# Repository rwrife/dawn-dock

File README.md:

A USB-powered ESP32-S3 bedside clock that keeps time and alarms offline, syncs user-approved schedules from a phone or PC, dims for sleep, and remains useful without internet.

## Overview

Dawn Dock sits between a basic alarm clock and a cloud-dependent smart display. Its core clock, alarm, snooze, brightness, and local setup functions work without an account or network. A companion app can transfer alarm schedules and calendar snapshots over the local network or BLE; optional weather and calendar refreshes are additive, never prerequisites for waking.

## Motivation

Traditional alarm clocks are dependable but tedious to configure. Smart displays are convenient but can depend on vendor accounts, internet services, microphones, and opaque data handling. Dawn Dock aims for a repairable middle path: physical controls, a calm night display, RTC-backed timekeeping, explicit sync, and documented offline behavior.

## Target users

- People who want a bedside clock without a cloud account or always-listening microphone.
- Shift workers, students, caregivers, and households with changing but non-critical routines.
- Makers who want an approachable ESP32-S3 and KiCad project with modular bring-up.
- Privacy-conscious users who want to own, inspect, back up, and export alarm data.

Dawn Dock is a convenience appliance, not a life-safety or medical device. Users must not rely on it for medication, emergency response, transportation safety, or any situation where a missed alarm could cause serious harm.

## Concrete use cases

1. Set recurring weekday alarms on the device with a rotary control and dedicated buttons.
2. Prepare a week of alarms on a phone or computer, review a diff, and explicitly sync it to the clock.
3. Import selected events from an `.ics` file and turn them into alarm suggestions that require confirmation.
4. Dim the screen manually or with an ambient-light rule while retaining a one-press brightness override.
5. Lose Wi-Fi overnight and still get the stored alarm from RTC-backed local state.
6. Export alarms, settings, and a redacted event snapshot as portable JSON.

## Intended workflow

1. Assemble the ESP32-S3 display module, low-voltage carrier board, controls, sensor, and enclosure.
2. Flash firmware over USB and complete first-run setup locally.
3. Set time from the companion app, USB serial, or network time; the RTC maintains time across normal power interruptions.
4. Create alarms on-device or in the companion app. Calendar-derived alarms are previews until accepted.
5. Review the device/app sync summary, transfer the schedule, and verify the next alarm on the clock face.
6. Use physical snooze, alarm-dismiss, brightness, and menu controls without opening the app.
7. Export or restore user-owned configuration when moving devices.

## MVP features

- RTC-backed local time, timezone, DST rules, and deterministic recurring alarms.
- 3.5-inch readable clock face with manual and ambient-light-aware dimming.
- Dedicated snooze and brightness controls plus a rotary menu control.
- Locally stored alarms with clear next-alarm and sync-state indicators.
- Local-only companion setup/sync, schedule preview, JSON backup, and `.ics` import.
- Versioned, authenticated local protocol with no required cloud account.
- Repeatable firmware/app builds and hardware-in-the-loop test points as the project matures.

## Non-goals

- No voice assistant, microphone monitoring, advertising, or remote cloud dashboard.
- No automatic alarm creation from calendar events without user confirmation.
- No news feed in the MVP; weather is optional and must fail quietly when offline.
- No battery operation beyond RTC backup in the first revision.
- No mains circuitry, custom AC adapter, medical claims, emergency alerts, or guaranteed wake-up claim.
- No attempt to compete with tablets or general-purpose smart displays.

## Hardware direction

The Rev A component gate selected an Espressif `ESP32-S3-DEVKITC-1-N8R8` controller, a separate Waveshare `29318` 3.5-inch capacitive-touch display, an Analog Devices `DS3231MZ+` RTC with a non-rechargeable CR2032, and a microphone-free MAX98357A audio path. The editable KiCad carrier schematic now provides controls, sensing, protected USB-C input, test access, and mounting intent. The integrated Waveshare `ESP32-S3-Touch-LCD-3.5` candidate was rejected because it includes a fitted microphone and does not expose all required internal test nodes.

The source-backed decision, dated price/availability snapshot, unresolved physical gates, and proposed GPIO map are in [component validation](docs/component-validation.md), [the preliminary BOM](bom/preliminary-bom.csv), and [the pin allocation](hardware/pin-allocation.csv).

The editable design tree is:

```text
hardware/kicad/dawn-dock.kicad_pro
hardware/kicad/dawn-dock.kicad_sch
hardware/kicad/dawn-dock.kicad_pcb  # routed Rev A0 review source
```

The project, schematic, and routed two-layer PCB exist and remain the design source of truth. Native ERC and DRC are clean and the review-only Gerber bundle is complete/aligned, but issue #4 remains on fabrication hold for received-unit geometry/orientation confirmation and unresolved EMC return-path/plane-coverage findings. PDF, render, and Gerber exports supplement but never replace editable sources.

Final electrical BOM data lives in KiCad schematic symbol properties (`Manufacturer`, `MPN`, supplier fields, notes) and is exported to `bom/bom.csv`. `bom/preliminary-bom.csv` is planning input/history, not the final electrical BOM.

## Privacy, permissions, and storage

- Device schedules and settings remain in local flash; the companion stores its local copy on the user's device.
- No account or telemetry is required. Network discovery and calendar/file access are requested only when the user invokes those workflows.
- Calendar import is file-based or user-selected; the MVP does not request broad calendar access by default.
- Sync is limited to the local network or BLE, uses an explicit pairing step, and presents changes before applying them.
- Backup/export uses documented JSON; calendar import uses `.ics`. Users can delete device/app state.
- Optional external data such as weather must be opt-in, disclose the contacted endpoint, and never affect alarm execution.

## Safety limits

- USB 5 V SELV power only; no mains wiring or charger design.
- Use a certified, enclosed USB power supply. Do not operate damaged cables or exposed assemblies unattended.
- RTC coin-cell support, if used, must follow the holder and cell manufacturer's polarity, chemistry, and charging restrictions.
- Audio output must be volume-limited and verified; the prototype is not a hearing or emergency alert device.
- Bench, simulation, and static-analysis results must be labeled separately. An unbuilt prototype is never described as physically tested.

## Architecture and verification baseline

The v0.1 documentation baseline freezes downstream design constraints while keeping unverified performance explicit:

- [System architecture and power allocation](docs/system-architecture.md)
- [Deterministic alarm semantics](docs/alarm-semantics.md)
- [MVP threat model](docs/threat-model.md)
- [Risk register](docs/risk-register.md)
- [Requirements verification matrix](docs/verification-matrix.md)
- [Hardware and product requirements](hardware/requirements.md)
- [Rev A component validation](docs/component-validation.md)
- [Manufacturer/source manifest](docs/source-manifest.csv)
- [Editable KiCad schematic, build, and verification](hardware/kicad/README.md)
- [Rev A schematic static review](docs/schematic-review.md)
- [Rev A0 PCB static layout review and fabrication hold](docs/pcb-layout-review.md)

The diagrams are editable Mermaid source. Results must be labeled as static analysis, simulation, software test, bench test, or field test; an absent physical test remains an open evidence gap.

## Current status and milestones

**Status: requirements, Rev A component selection, schematic, a routed Rev A0 PCB review candidate, host-tested firmware cores, and a Flutter companion with host-tested local-only demo screens including a simulated in-memory pairing review route exist; fabrication and parent companion issue #6 remain open.** The Android/iOS companion scaffold is pinned to Flutter 3.47.2 / Dart 3.13.2 and its widget tests exercise an offline in-memory review, cancel, explicit fake apply, revision receipt, reset, same-process widget reconstruction, and accessibility behavior. They do not exercise an app process restart or device relaunch; reset after a real restart is only the intended result of the non-persistent implementation. The Dart demo implements no real pairing, transport, persistence, calendar integration, alarm execution, network behavior, runtime permission request, or protocol conformance. A host-tested pure-Dart domain layer now exists beside it (`app/lib/domain/`: canonical protocol-fixture contract mirror, device profiles, bounded alarm drafts, revision-tracked schedule mirror, versioned fail-closed JSON backup, a local backup flow coordinator (export/inspect/restore with stale-restore guard and idempotent erase), a host-tested backup-flow presentation state controller (serialized actions plus busy/absent/success/failure and explicit stale-confirmation states), a host-tested accessible backup panel widget that renders those controller states as text-only status with disabled-while-busy actions and explicit stale confirmation (tested over an in-memory store double), now mounted via a host-tested demo backup page behind an "Open backup demo" navigation entry over a real caller-injected temporary-directory file store (host filesystem tests only, with no path_provider platform storage, file picker, or encryption), a deterministic reviewable schedule-diff core, a host-tested accessible schedule-review panel and demo page that render that diff locally (host widget evidence only; no preview/apply envelope is ever sent and no device apply token exists or is validated), schedule preview/apply exchange framing with token binding and revision-conflict handling, a host-tested schedule-flow presentation controller requiring explicit review and apply confirmation before a supplied consistent receipt advances the local mirror, plus a host-tested accessible flow panel mounted in a seeded in-memory demo route that frames but never delivers a preview (issues #63/#65/#67; no token/receipt simulation, authenticated transport, or device evidence), a pure-Dart mirror of the firmware weekly recurrence resolver with gap/fold fixtures matching the firmware test instants, a fail-closed device-status/next-alarm projection, and a pairing policy state machine with bounded candidate records, a 120-second/5-attempt ceremony, and opaque secure-storage references), but none of it is yet wired to a real transport flow with platform secure storage, cryptography, discovery, or a user file picker. Android debug/profile manifests nevertheless declare `INTERNET` for Flutter development tooling, and iOS development tooling may use the local network. The development build gates do not prove release permission configuration. KiCad and firmware software/static evidence remains as documented in the verification matrix. No enclosure, assembled prototype, or physical test result exists yet; current, luminance, acoustic, retention, mechanical, EMC/ESD, thermal, physical screen-reader, and device usability evidence remain open. The status projection is now also rendered in a host-tested local-only demo view over a fixed fixture anchor with synthetic receipt cases; it does not indicate live device status, nor use a platform clock or timezone database.

Host-only local-data erase coordination now removes the caller-owned backup file before clearing injected in-memory profile, draft, and schedule stores (including revision/receipt). File deletion failure preserves live stores; repeat calls are safe. This method has no UI wiring and does not touch platform-private storage, credentials, or real device data.

1. **Requirements and risk baseline** — v0.1 architecture, alarm semantics, measurable targets, threat model, risk register, and evidence matrix documented.
2. **Component validation complete for schematic capture** — selected architecture, pin/resource allocation, dated sourcing snapshot, and evidence gaps are documented.
3. **Editable carrier schematic complete** — native ERC 0 errors/0 warnings, analyzer evidence, critical pin mapping, and KiCad-derived BOM are committed.
4. Continue the firmware from the tested occurrence and dual-slot storage cores into recurrence/timezone, ESP-IDF NVS integration, and hardware abstractions while Rev A0 fabrication holds remain open.
5. Continue open issue #6 from the fake-only companion bootstrap into reviewed pairing, persistence, calendar, and authenticated protocol integration. Host-tested ICS suggestions reject nonzero DTSTART seconds, conflicting named TZID plus UTC Z, all-day DATE with TZID, and explicit DTSTART VALUE mismatches/unsupported types instead of guessing an alarm time or zone; valid neighbors remain reviewable. Repeated DTSTART TZID/VALUE parameters are dropped before alarm review with value-free notices, including mixed-case and identical duplicates. Cross-file reconciliation, platform file import, and device integration remain open.
6. Integrate, assemble, measure, troubleshoot, and publish fabrication/release evidence.

See [PLAN.md](PLAN.md), [hardware/requirements.md](hardware/requirements.md), and the issue backlog.

## Development quickstart

Validate documentation, selected components, and committed schematic evidence with:

```bash
python3 scripts/check_docs.py
python3 scripts/check_component_selection.py
```

The hardware validator intentionally requires fresh KiCad-derived inputs; use
the complete command sequence in [`hardware/kicad/README.md`](hardware/kicad/README.md).

Implementation tools:

- KiCad 9 or newer for editable schematic/PCB work and ERC/DRC.
- ESP-IDF 5.x with CMake/Ninja for firmware.
- Flutter 3.47.2 with bundled Dart 3.13.2 for the current Android/iOS companion scaffold; Windows/macOS are not enabled yet.
- Python 3 for protocol fixtures and hardware-independent integration tests.

Run the companion software checks with:

```bash
cd app
FLUTTER_BIN=/tmp/flutter-3.47.2/bin/flutter ./tool/verify_flutter_version.sh
/tmp/flutter-3.47.2/bin/flutter pub get --enforce-lockfile
/tmp/flutter-3.47.2/bin/dart format --output=none --set-exit-if-changed lib test
/tmp/flutter-3.47.2/bin/flutter analyze
/tmp/flutter-3.47.2/bin/flutter test --coverage
```

See [`app/README.md`](app/README.md) for the offline-demo boundary, mobile workflow, CI build gates, desktop enablement command, and accessibility gaps. See [`hardware/kicad/README.md`](hardware/kicad/README.md) for the pinned hardware workflow and [`firmware/README.md`](firmware/README.md) for host tests, the immutable ESP-IDF container build, flash/recovery commands, and explicit firmware evidence gaps.

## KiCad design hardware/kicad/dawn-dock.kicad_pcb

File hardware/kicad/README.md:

# Dawn Dock KiCad source

This directory contains the editable Rev A carrier schematic and routed two-layer PCB. These are static design artifacts only: there is no fabricated assembly or bench evidence yet.

## Files

- `dawn-dock.kicad_pro` / `dawn-dock.kicad_sch` / `dawn-dock.kicad_pcb` — KiCad 9 project, schematic, and routed PCB.
- `lib/dawn-dock.kicad_sym` — project symbols derived from cited manufacturer pin tables.
- `lib/dawn-dock.pretty/` — project footprints for the DevKit/socket, module headers, PEC11R, and Keystone 3003.
- `generate_schematic.py` — reproducible source generator.
- `generate_pcb.py` — deterministic board outline, placement, antenna rule area, and fine-pitch fanout generator from a fresh KiCad netlist.
- `specctra_io.py` — KiCad-native DSN export / SES import bridge with current-aware routing classes.
- `finalize_pcb.py` — deterministic final +5 V join, GND stitching, and filled dual-layer GND planes.
- `export_fabrication.py` — reproducible review-only Gerber/drill/placement/render export and checksum generator.
- `validate_hardware.py` — BOM/connectivity/evidence assertions.
- `reports/erc.rpt` — native KiCad 9 ERC output.
- `reports/drc.json` — native KiCad 9 PCB DRC/parity output for the committed board.
- `reports/schematic-analysis.json` / `.txt` — static analyzer output.
- `reports/pcb.json`, `cross-analysis.json`, `emc.json`, `thermal.json`, and `gerber.json` — layout/cross-domain risk evidence and disclosed gaps.
- `reports/hardware-validation.json` — project-specific machine-readable checks.
- `fabrication/README.md` / `fabrication/rev-a0-prototype-review/` — checked review bundle under an explicit fabrication hold.

## Rebuild

Use KiCad 9 symbol libraries and Python 3.11+:

```bash
python3 -m venv .venv
.venv/bin/pip install -r hardware/kicad/requirements.txt
.venv/bin/python hardware/kicad/generate_schematic.py \
  --symbol-dir /usr/share/kicad/symbols
```

The schematic generator rewrites the project-local symbol and footprint files and the schematic. UUIDs may change between generations; review the electrical diff, not only textual UUID churn.

## Rebuild and route the PCB

The accepted Rev A board was built with KiCad `9.0.2+dfsg-1`, FreeRouting `2.3.0`, and Eclipse Temurin `25.0.4+7`. FreeRouting is nondeterministic; the committed `.kicad_pcb` is the reviewed editable result. The deterministic generator/finalizer and these commands make rerouting auditable, but a new SES result must pass the same DRC before replacing the committed board.

```bash
docker build -t dawn-dock-kicad-verify \
  -f hardware/kicad/Dockerfile.verify hardware/kicad

route_dir="$(mktemp -d)"
curl -fL \
  https://github.com/freerouting/freerouting/releases/download/v2.3.0/freerouting-2.3.0.jar \
  -o "$route_dir/freerouting-2.3.0.jar"
printf '%s  %s\n' \
  '3cf18d608437740bc497db6b8ef5888e2e60a08de0def20691d1bad0c0e0ee24' \
  "$route_dir/freerouting-2.3.0.jar" | sha256sum --check

docker run --rm -v "$PWD:/work" -v "$route_dir:/route" -w /work \
  dawn-dock-kicad-verify sch export netlist \
  --output /route/dawn-dock.net hardware/kicad/dawn-dock.kicad_sch
docker run --rm -v "$PWD:/work" -v "$route_dir:/route" -w /work \
  --entrypoint python3 dawn-dock-kicad-verify \
  hardware/kicad/generate_pcb.py --netlist /route/dawn-dock.net \
  --output hardware/kicad/dawn-dock.kicad_pcb
docker run --rm -v "$PWD:/work" -v "$route_dir:/route" -w /work \
  --entrypoint python3 dawn-dock-kicad-verify \
  hardware/kicad/specctra_io.py export \
  --board hardware/kicad/dawn-dock.kicad_pcb --dsn /route/dawn-dock.dsn
docker run --rm -v "$route_dir:/route" eclipse-temurin:25-jre \
  java -jar /route/freerouting-2.3.0.jar \
  -de /route/dawn-dock.dsn -do /route/dawn-dock.ses \
  -mp 30 -mt 4 -da --gui.enabled=false \
  --logging.file.enabled=false --logging.console.level=INFO \
  --user_data_path=/tmp/freerouting
docker run --rm -v "$PWD:/work" -v "$route_dir:/route" -w /work \
  --entrypoint python3 dawn-dock-kicad-verify \
  hardware/kicad/specctra_io.py import \
  --board hardware/kicad/dawn-dock.kicad_pcb --ses /route/dawn-dock.ses \
  --output /route/dawn-dock-routed.kicad_pcb
docker run --rm -v "$PWD:/work" -v "$route_dir:/route" -w /work \
  --entrypoint python3 dawn-dock-kicad-verify \
  hardware/kicad/finalize_pcb.py --board /route/dawn-dock-routed.kicad_pcb \
  --output hardware/kicad/dawn-dock.kicad_pcb
```

## Verify

Native KiCad 9 ERC:

```bash
kicad-cli sch erc \
  --output hardware/kicad/reports/erc.rpt \
  --exit-code-violations \
  hardware/kicad/dawn-dock.kicad_sch
```

Schematic analyzer (from `kicad-happy`):

```bash
python3 /path/to/kicad-happy/skills/kicad/scripts/analyze_schematic.py \
  hardware/kicad/dawn-dock.kicad_sch \
  --output hardware/kicad/reports/schematic-analysis.json
python3 /path/to/kicad-happy/skills/kicad/scripts/analyze_schematic.py \
  hardware/kicad/dawn-dock.kicad_sch --text \
  > hardware/kicad/reports/schematic-analysis.txt
```

Export the source-property BOM with KiCad 9:

```bash
kicad-cli sch export bom hardware/kicad/dawn-dock.kicad_sch \
  --output bom/bom.csv \
  --fields 'Reference,${QUANTITY},Value,Footprint,Manufacturer,MPN,Supplier,Supplier PN,Estimated Unit Cost USD,Price Observed UTC,BOM Comments,${DNP}' \
  --labels 'Reference,Qty,Value,Footprint,Manufacturer,MPN,Supplier,Supplier_PN,Estimated_Unit_Cost_USD,Price_Observed_UTC,Notes,DNP' \
  --group-by 'Value,Footprint,Manufacturer,MPN,Supplier,Supplier PN,Estimated Unit Cost USD,Price Observed UTC,BOM Comments,${DNP}' \
  --sort-field Reference --sort-asc
```

Export a fresh netlist and then run the project gate with explicit fresh inputs:

```bash
kicad-cli sch export netlist --output /tmp/dawn-dock.net \
  hardware/kicad/dawn-dock.kicad_sch
python3 hardware/kicad/validate_hardware.py \
  --netlist /tmp/dawn-dock.net \
  --bom bom/bom.csv \
  --erc hardware/kicad/reports/erc.rpt
python3 scripts/check_component_selection.py
python3 scripts/check_docs.py
```

CI does not trust these committed evidence files in isolation. It builds
`Dockerfile.verify`, runs KiCad 9 ERC, exports a fresh netlist and BOM from the
checked-out schematic, byte-compares the fresh BOM with `bom/bom.csv`, and calls
`validate_hardware.py --netlist ... --bom ... --erc ...` on those fresh outputs.
The validator intentionally has no stale-report fallback: all three inputs are required.

## Verified design facts

- USB-C is a 5 V sink only. CC1 and CC2 have independent 5.1 kΩ Rd resistors; D+/D-/SBU are NC.
- `TPS259531DSGR` pin mapping follows TI SLVSE57C: dVdt 1, EN/UVLO 2, IN 3/4, OUT 5, FLT 6, ILM 7, GND 8/EP.
- `R_ILIM=1.53 kΩ`: TI equation 4 gives approximately 1.347 A nominal; the documented +7.5% limit/-1% resistor bound is approximately 1.463 A.
- `C_DVDT=100 nF`: TI equation 3 gives approximately 0.42 V/ms, or 11.9 ms to 5 V. With the explicitly fitted 480 µF output capacitance, the modeled capacitor inrush is approximately 202 mA; module-internal capacitance still requires measurement.
- DS3231MZ+ uses the manufacturer SO-8 pin map. VBAT connects only to the CR2032 positive terminal; there is no charging component or rail tie.
- SN74LVC14APWR uses TI's TSSOP-14 mapping. Five inputs receive separate 5 V/4.7 kΩ wetted contacts; outputs are 3.3 V logic. The unused sixth input is tied low and its output is NC.
- DevKit header pins follow Espressif DevKitC-1 v1.1. N8R8-reserved GPIO35–37, strap pins 3/45/46, onboard RGB GPIO38, and native USB GPIO19/20 are not application loads.
- Waveshare 29318 logic uses its manufacturer-listed SPI/I²C signals. Its 15-pin socket orientation and the received module revision must be rechecked before PCB placement/fabrication.

## Intentional analyzer exceptions

The generic schematic analyzer reports 5 V/3.3 V crossings on `I2C_SDA`, `I2C_SCL`, and `RTC_INT_N`. These are static-classification false positives: the Waveshare display explicitly includes level conversion and supports 3.3 V logic while powered from 5 V; the Adafruit 4162 is powered from 3.3 V; DS3231MZ+ is powered and pulled up at 3.3 V. No 5 V pull-up is fitted on those nets.

The optional carrier I²C pull-ups are DNP because the display and sensor modules include pull-ups. Populate only after measuring aggregate resistance/rise time on received modules.

## Open evidence gates

- The routed Rev A0 board and review-only manufacturing outputs exist, but six error-level heuristic plane-coverage findings and two error-level clock-transition return-path findings remain open. The finalizer added 59 DRC-clean return vias; see `reports/emc.json` and `fabrication/README.md`.
- Exact received-unit dimensions, connector orientation, enclosure/mechanical placement, and antenna metal clearance still block fabrication.
- Module revision, connector orientation, total module capacitance, current, luminance, audio, RTC retention/drift, ESD/EMC, and thermals require identified physical hardware.
- Price and availability are dated 2026-08-23 planning observations, not purchase-time guarantees.
- The local analyzer has no structured datasheet extraction cache, so its trust rollup remains low even though critical pin tables were manually checked against downloaded manufacturer PDFs. Do not convert this static review into a bench-tested or fabrication-ready claim.

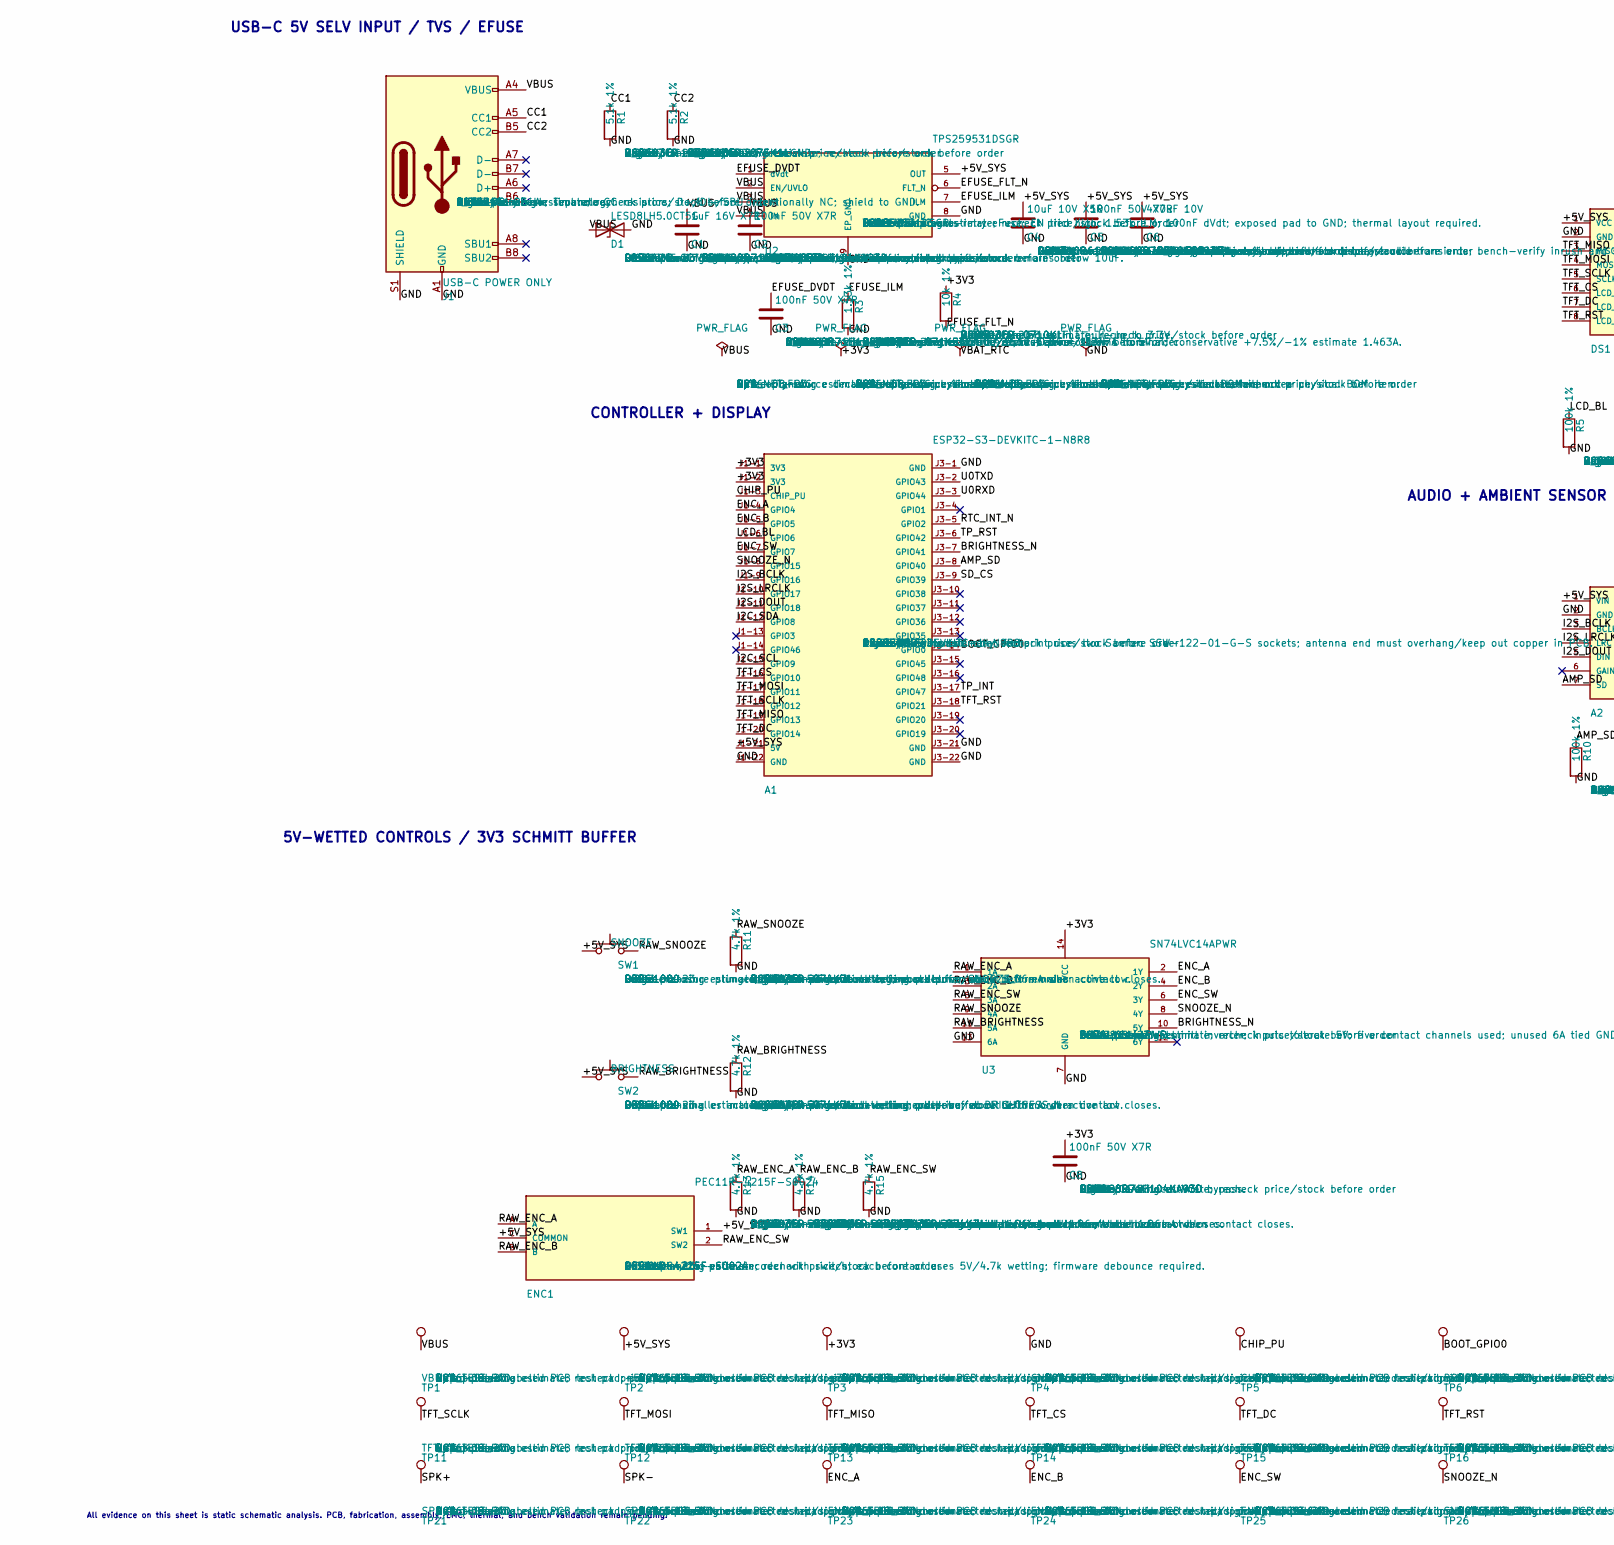
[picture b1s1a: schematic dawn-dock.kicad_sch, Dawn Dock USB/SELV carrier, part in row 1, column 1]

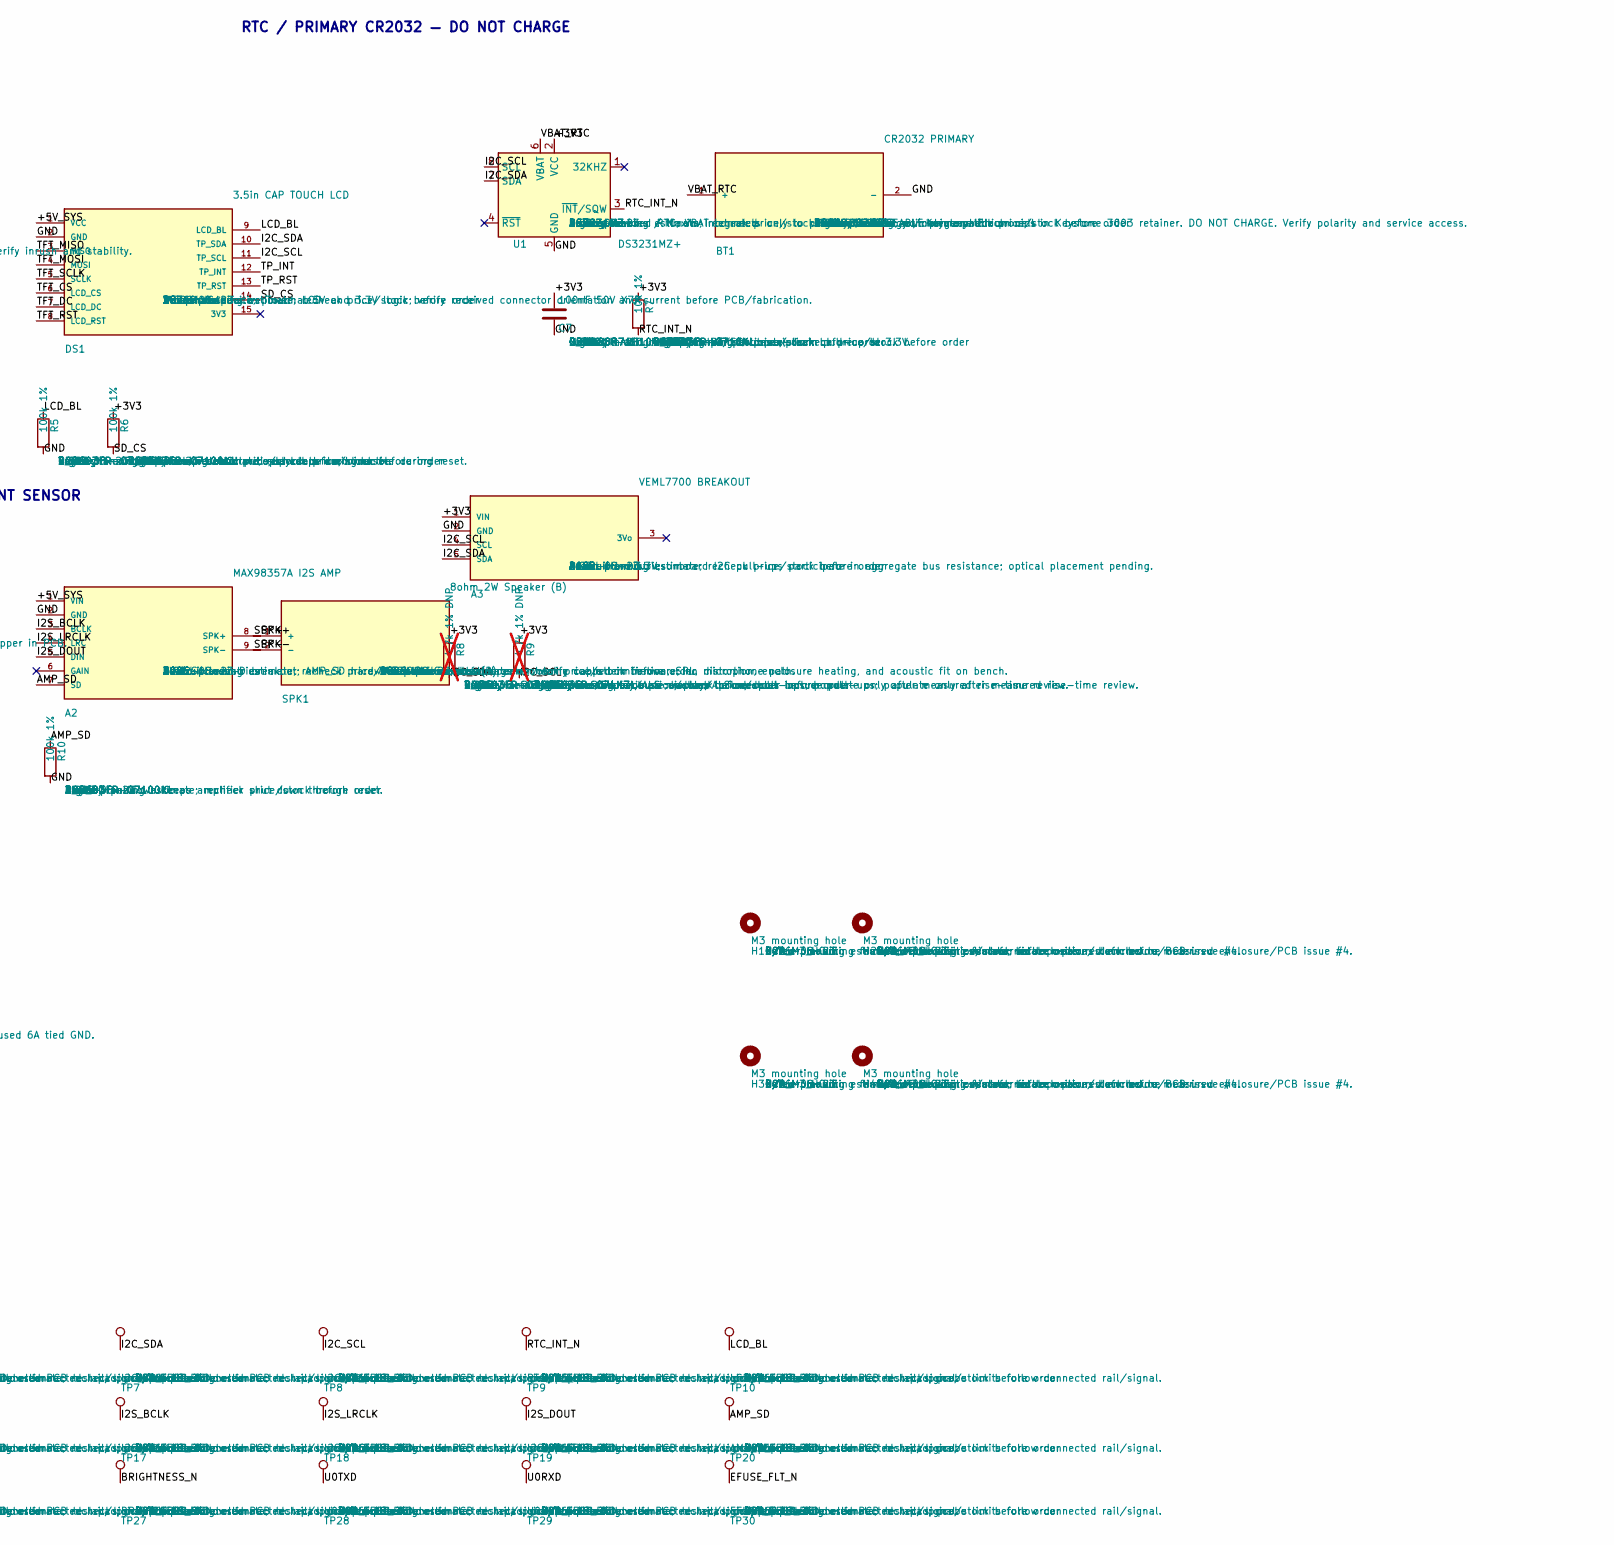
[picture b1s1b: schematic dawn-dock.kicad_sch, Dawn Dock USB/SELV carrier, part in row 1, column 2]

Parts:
A1: ESP32-S3-DEVKITC-1-N8R8; ESP32-S3-DevKitC-1_Socket; MPN ESP32-S3-DEVKITC-1-N8R8
A2: MAX98357A I2S AMP; Adafruit_3006_MAX98357A; MPN 3006
A3: VEML7700 BREAKOUT; Adafruit_4162_VEML7700; MPN 4162
BT1: CR2032 PRIMARY; Keystone_3003_CR2032; MPN CR2032; 3003
C1: 1uF 16V X7R; C_0603_1608Metric; MPN GRM188R71C105KA12D
C2, C3, C5, C7, C8: 100nF 50V X7R; C_0603_1608Metric; MPN GRM188R71H104KA93D
C4: 10uF 10V X5R; C_1206_3216Metric; MPN GRM31CR61A106KA01L
C6: 470uF 10V; C_Radial_D8.0mm_H11.5mm_P3.50mm; MPN EEU-FR1A471
D1: LESD8LH5.0CT5G; D_SOD-882; MPN LESD8LH5.0CT5G
DS1: 3.5in CAP TOUCH LCD; PinSocket_1x15_P2.54mm_Vertical; MPN 3.5inch Capacitive Touch LCD
ENC1: PEC11R-4215F-S0024; PEC11R-4xxxF-Sxxxx; MPN PEC11R-4215F-S0024
H1, H2, H3, H4: M3 mounting hole; MountingHole_3.2mm_M3; MPN PCB_M3_HOLE
J1: USB-C POWER ONLY; USB_C_Receptacle_GCT_USB4105-xx-A_16P_TopMnt_Horizontal; MPN USB4105-GF-A
R1, R2: 5.1k 1%; R_0603_1608Metric; MPN RC0603FR-075K1L
R3: 1.53k 1%; R_0603_1608Metric; MPN RC0603FR-071K53L
R4, R7: 10k 1%; R_0603_1608Metric; MPN RC0603FR-0710KL
R5, R6, R10: 100k 1%; R_0603_1608Metric; MPN RC0603FR-07100KL
R8, R9: 4.7k 1% DNP; R_0603_1608Metric; MPN RC0603FR-074K7L; not fitted
R11, R12, R13, R14, R15: 4.7k 1%; R_0603_1608Metric; MPN RC0603FR-074K7L
SPK1: 8ohm 2W Speaker (B); MPN 8ohm 2W Speaker (B)
SW1: SNOOZE; SW_TH_Tactile_Omron_B3F-10xx; MPN B3F-1000
SW2: BRIGHTNESS; SW_TH_Tactile_Omron_B3F-10xx; MPN B3F-1000
TP1: VBUS; TestPoint_Pad_D1.5mm; MPN PCB_TEST_PAD
TP2: +5V_SYS; TestPoint_Pad_D1.5mm; MPN PCB_TEST_PAD
TP3: +3V3; TestPoint_Pad_D1.5mm; MPN PCB_TEST_PAD
TP4: GND; TestPoint_Pad_D1.5mm; MPN PCB_TEST_PAD
TP5: CHIP_PU; TestPoint_Pad_D1.5mm; MPN PCB_TEST_PAD
TP6: BOOT_GPIO0; TestPoint_Pad_D1.5mm; MPN PCB_TEST_PAD
TP7: I2C_SDA; TestPoint_Pad_D1.5mm; MPN PCB_TEST_PAD
TP8: I2C_SCL; TestPoint_Pad_D1.5mm; MPN PCB_TEST_PAD
TP9: RTC_INT_N; TestPoint_Pad_D1.5mm; MPN PCB_TEST_PAD
TP10: LCD_BL; TestPoint_Pad_D1.5mm; MPN PCB_TEST_PAD
TP11: TFT_SCLK; TestPoint_Pad_D1.5mm; MPN PCB_TEST_PAD
TP12: TFT_MOSI; TestPoint_Pad_D1.5mm; MPN PCB_TEST_PAD
TP13: TFT_MISO; TestPoint_Pad_D1.5mm; MPN PCB_TEST_PAD
TP14: TFT_CS; TestPoint_Pad_D1.5mm; MPN PCB_TEST_PAD
TP15: TFT_DC; TestPoint_Pad_D1.5mm; MPN PCB_TEST_PAD
TP16: TFT_RST; TestPoint_Pad_D1.5mm; MPN PCB_TEST_PAD
TP17: I2S_BCLK; TestPoint_Pad_D1.5mm; MPN PCB_TEST_PAD
TP18: I2S_LRCLK; TestPoint_Pad_D1.5mm; MPN PCB_TEST_PAD
TP19: I2S_DOUT; TestPoint_Pad_D1.5mm; MPN PCB_TEST_PAD
TP20: AMP_SD; TestPoint_Pad_D1.5mm; MPN PCB_TEST_PAD
TP21: SPK+; TestPoint_Pad_D1.5mm; MPN PCB_TEST_PAD
TP22: SPK-; TestPoint_Pad_D1.5mm; MPN PCB_TEST_PAD
TP23: ENC_A; TestPoint_Pad_D1.5mm; MPN PCB_TEST_PAD
TP24: ENC_B; TestPoint_Pad_D1.5mm; MPN PCB_TEST_PAD
TP25: ENC_SW; TestPoint_Pad_D1.5mm; MPN PCB_TEST_PAD
TP26: SNOOZE_N; TestPoint_Pad_D1.5mm; MPN PCB_TEST_PAD
TP27: BRIGHTNESS_N; TestPoint_Pad_D1.5mm; MPN PCB_TEST_PAD
TP28: U0TXD; TestPoint_Pad_D1.5mm; MPN PCB_TEST_PAD
TP29: U0RXD; TestPoint_Pad_D1.5mm; MPN PCB_TEST_PAD
TP30: EFUSE_FLT_N; TestPoint_Pad_D1.5mm; MPN PCB_TEST_PAD
U1: DS3231MZ+; SOIC-8_3.9x4.9mm_P1.27mm; MPN DS3231MZ+
U2: TPS259531DSGR; WSON-8-1EP_2x2mm_P0.5mm_EP0.9x1.6mm_ThermalVias; MPN TPS259531DSGR
U3: SN74LVC14APWR; TSSOP-14_4.4x5mm_P0.65mm; MPN SN74LVC14APWR

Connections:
/+3V3: A1.J1-1 (3V3), A1.J1-2 (3V3), A3.1 (VIN), C7.1, C8.1, R4.1, R6.1, R7.1, R8.1, R9.1, TP3.1, U1.2 (VCC), U3.14 (VCC)
/+5V_SYS: A1.J1-21 (5V), A2.1 (VIN), C4.1, C5.1, C6.1, DS1.1 (VCC), ENC1.1 (SW1), ENC1.C (COMMON), SW1.1, SW2.1, TP2.1, U2.5 (OUT)
/AMP_SD: A1.J3-8 (GPIO40), A2.7 (SD), R10.1, TP20.1
/BOOT_GPIO0: A1.J3-14 (GPIO0), TP6.1
/BRIGHTNESS_N: A1.J3-7 (GPIO41), TP27.1, U3.10 (5Y)
/CC1: J1.A5 (CC1), R1.1
/CC2: J1.B5 (CC2), R2.1
/CHIP_PU: A1.J1-3 (CHIP_PU), TP5.1
/EFUSE_DVDT: C3.1, U2.1 (dVdt)
/EFUSE_FLT_N: R4.2, TP30.1, U2.6 (FLT_N)
/EFUSE_ILM: R3.1, U2.7 (ILM)
/ENC_A: A1.J1-4 (GPIO4), TP23.1, U3.2 (1Y)
/ENC_B: A1.J1-5 (GPIO5), TP24.1, U3.4 (2Y)
/ENC_SW: A1.J1-7 (GPIO7), TP25.1, U3.6 (3Y)
/GND: A1.J1-22 (GND), A1.J3-1 (GND), A1.J3-21 (GND), A1.J3-22 (GND), A2.2 (GND), A3.2 (GND), BT1.2 (-), C1.2, C2.2, C3.2, C4.2, C5.2, C6.2, C7.2, C8.2, D1.2 (A2), DS1.2 (GND), J1.A1 (GND), J1.A12 (GND), J1.B1 (GND), J1.B12 (GND), J1.S1 (SHIELD), R1.2, R2.2, R3.2, R5.2, R10.2, R11.2, R12.2, R13.2, R14.2, R15.2, TP4.1, U1.5 (GND), U2.8 (GND), U2.9 (EP_GND), U3.7 (GND), U3.13 (6A)
/I2C_SCL: A1.J1-15 (GPIO9), A3.4 (SCL), DS1.11 (TP_SCL), R9.2, TP8.1, U1.8 (SCL)
/I2C_SDA: A1.J1-12 (GPIO8), A3.5 (SDA), DS1.10 (TP_SDA), R8.2, TP7.1, U1.7 (SDA)
/I2S_BCLK: A1.J1-9 (GPIO16), A2.3 (BCLK), TP17.1
/I2S_DOUT: A1.J1-11 (GPIO18), A2.5 (DIN), TP19.1
/I2S_LRCLK: A1.J1-10 (GPIO17), A2.4 (LRC), TP18.1
/LCD_BL: A1.J1-6 (GPIO6), DS1.9 (LCD_BL), R5.1, TP10.1
/RAW_BRIGHTNESS: R12.1, SW2.2, U3.11 (5A)
/RAW_ENC_A: ENC1.A, R13.1, U3.1 (1A)
/RAW_ENC_B: ENC1.B, R14.1, U3.3 (2A)
/RAW_ENC_SW: ENC1.2 (SW2), R15.1, U3.5 (3A)
/RAW_SNOOZE: R11.1, SW1.2, U3.9 (4A)
/RTC_INT_N: A1.J3-5 (GPIO2), R7.2, TP9.1, U1.3 (~INT/SQW)
/SD_CS: A1.J3-9 (GPIO39), DS1.14 (SD_CS), R6.2
/SNOOZE_N: A1.J1-8 (GPIO15), TP26.1, U3.8 (4Y)
/SPK+: A2.8 (SPK+), SPK1.1 (+), TP21.1
/SPK-: A2.9 (SPK-), SPK1.2 (-), TP22.1
/TFT_CS: A1.J1-16 (GPIO10), DS1.6 (LCD_CS), TP14.1
/TFT_DC: A1.J1-20 (GPIO14), DS1.7 (LCD_DC), TP15.1
/TFT_MISO: A1.J1-19 (GPIO13), DS1.3 (MISO), TP13.1
/TFT_MOSI: A1.J1-17 (GPIO11), DS1.4 (MOSI), TP12.1
/TFT_RST: A1.J3-18 (GPIO21), DS1.8 (LCD_RST), TP16.1
/TFT_SCLK: A1.J1-18 (GPIO12), DS1.5 (SCLK), TP11.1
/TP_INT: A1.J3-17 (GPIO47), DS1.12 (TP_INT)
/TP_RST: A1.J3-6 (GPIO42), DS1.13 (TP_RST)
/U0RXD: A1.J3-3 (GPIO44), TP29.1
/U0TXD: A1.J3-2 (GPIO43), TP28.1
/VBAT_RTC: BT1.1 (+), U1.6 (VBAT)
/VBUS: C1.1, C2.1, D1.1 (A1), J1.A4 (VBUS), J1.A9 (VBUS), J1.B4 (VBUS), J1.B9 (VBUS), TP1.1, U2.2 (EN/UVLO), U2.3 (IN), U2.4 (IN)

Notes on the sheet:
USB-C 5V SELV INPUT / TVS / EFUSE
CONTROLLER + DISPLAY
RTC / PRIMARY CR2032 — DO NOT CHARGE
AUDIO + AMBIENT SENSOR
5V-WETTED CONTROLS / 3V3 SCHMITT BUFFER
All evidence on this sheet is static schematic analysis. PCB, fabrication, assembly, EMC, thermal, and bench validation remain pending.

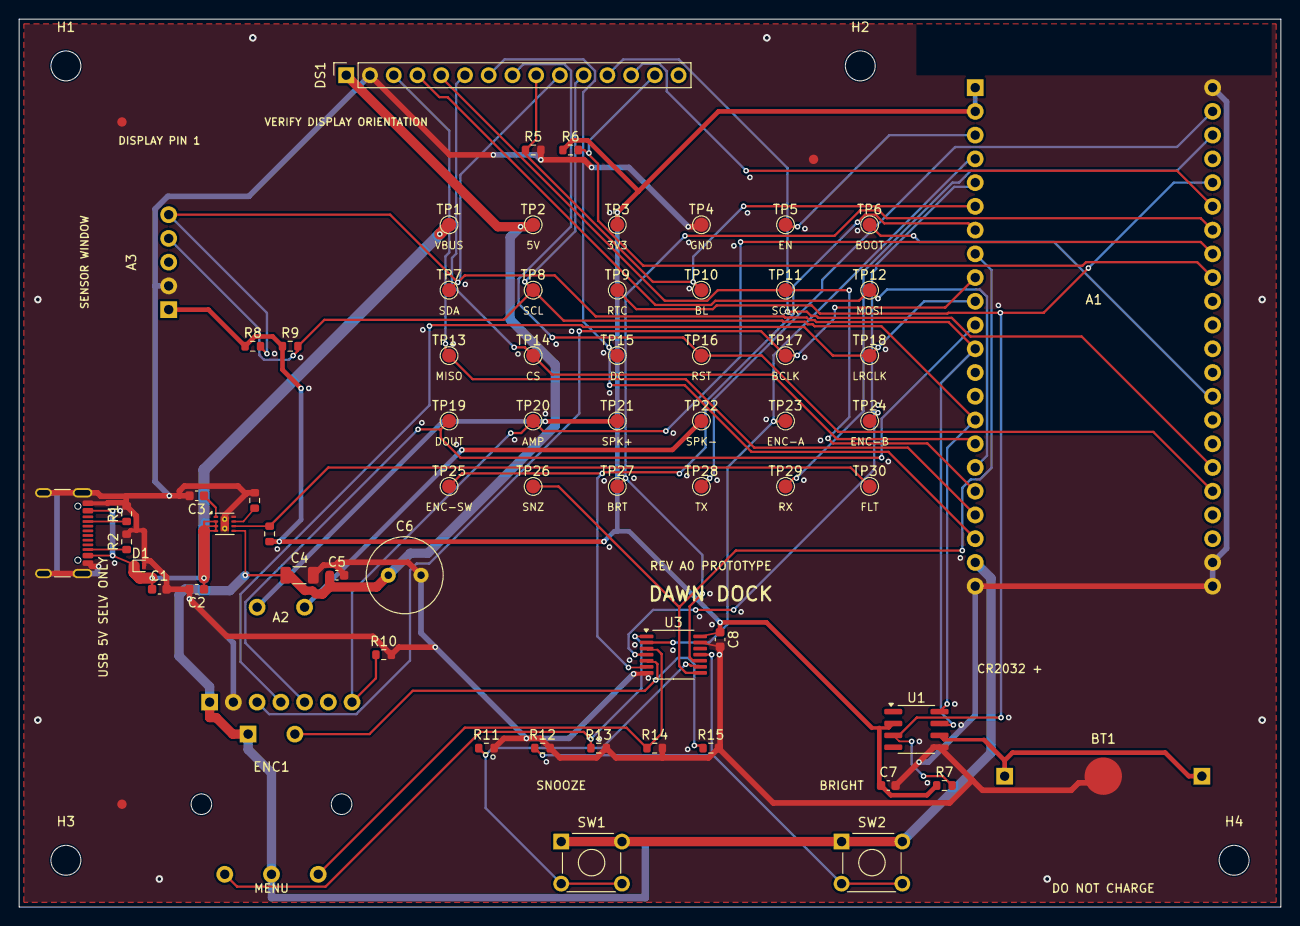
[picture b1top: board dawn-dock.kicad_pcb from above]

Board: 2 copper layers, 135.0 x 95.0 mm, 73 parts (0 on the bottom side), 43 nets.

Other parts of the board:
FID1, FID2, FID3: GLOBAL FIDUCIAL; Fiducial_1mm_Mask2mm

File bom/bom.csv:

"Reference","Qty","Value","Footprint","Manufacturer","MPN","Supplier","Supplier_PN","Estimated_Unit_Cost_USD","Price_Observed_UTC","Notes","DNP"
"A1","1","ESP32-S3-DEVKITC-1-N8R8","dawn-dock:ESP32-S3-DevKitC-1_Socket","Espressif Systems","ESP32-S3-DEVKITC-1-N8R8","DigiKey","15295894","13.9579","2026-08-23","Exact N8R8 module only; footprint uses two Samtec SSW-122-01-G-S sockets; antenna end must overhang/keep out copper in PCB.",""
"A2","1","MAX98357A I2S AMP","dawn-dock:Adafruit_3006_MAX98357A","Adafruit Industries","3006","Adafruit","3006","5.95","2026-08-23","5V I2S class-D breakout; AMP_SD hardware pulldown; default gain; volume capped in firmware; no microphone path.",""
"A3","1","VEML7700 BREAKOUT","dawn-dock:Adafruit_4162_VEML7700","Adafruit Industries","4162","Adafruit","4162","4.95","2026-08-23","Power from 3.3V; onboard I2C pull-ups participate in aggregate bus resistance; optical placement pending.",""
"BT1","1","CR2032 PRIMARY","dawn-dock:Keystone_3003_CR2032","Panasonic Energy / Keystone Electronics","CR2032; 3003","DigiKey","31939; 227448","1.25","2026-08-23","NON-RECHARGEABLE primary lithium cell in Keystone 3003 retainer. DO NOT CHARGE. Verify polarity and service access.",""
"C1","1","1uF 16V X7R","Capacitor_SMD:C_0603_1608Metric","Murata","GRM188R71C105KA12D","DigiKey","GRM188R71C105KA12D","0.08","2026-08-23","eFuse input bulk; USB-C sink-side nominal capacitance remains below 10uF.",""
"C2","1","100nF 50V X7R","Capacitor_SMD:C_0603_1608Metric","Murata","GRM188R71H104KA93D","DigiKey","GRM188R71H104KA93D","0.02","2026-08-23","TPS259531 high-frequency input bypass.",""
"C3","1","100nF 50V X7R","Capacitor_SMD:C_0603_1608Metric","Murata","GRM188R71H104KA93D","DigiKey","GRM188R71H104KA93D","0.02","2026-08-23","dVdt soft-start: TI Eq.3 gives about 0.42V/ms; about 11.9ms to 5V.",""
"C4","1","10uF 10V X5R","Capacitor_SMD:C_1206_3216Metric","Murata","GRM31CR61A106KA01L","DigiKey","GRM31CR61A106KA01L","0.3351","2026-08-23","Local protected-rail ceramic bulk.",""
"C5","1","100nF 50V X7R","Capacitor_SMD:C_0603_1608Metric","Murata","GRM188R71H104KA93D","DigiKey","GRM188R71H104KA93D","0.02","2026-08-23","Protected-rail high-frequency bypass.",""
"C6","1","470uF 10V","Capacitor_THT:C_Radial_D8.0mm_H11.5mm_P3.50mm","Panasonic Industry","EEU-FR1A471","DigiKey","EEU-FR1A471","0.80","2026-08-23","Low-ESR protected-rail bulk for display/audio transients; bench-verify inrush and stability.",""
"C7","1","100nF 50V X7R","Capacitor_SMD:C_0603_1608Metric","Murata","GRM188R71H104KA93D","DigiKey","GRM188R71H104KA93D","0.02","2026-08-23","DS3231M VCC decoupling per pin description.",""
"C8","1","100nF 50V X7R","Capacitor_SMD:C_0603_1608Metric","Murata","GRM188R71H104KA93D","DigiKey","GRM188R71H104KA93D","0.02","2026-08-23","SN74LVC14A local VCC bypass.",""
"D1","1","LESD8LH5.0CT5G","Diode_SMD:D_SOD-882","Leshan Radio Company","LESD8LH5.0CT5G","LCSC","C172420","0.0083","2026-08-23","Bidirectional VBUS TVS; place at connector with shortest ground return.",""
"DS1","1","3.5in CAP TOUCH LCD","Connector_PinSocket_2.54mm:PinSocket_1x15_P2.54mm_Vertical","Waveshare","3.5inch Capacitive Touch LCD","Waveshare","29318","18.99","2026-08-23","15-pin interface; power at 5V and 3.3V logic; verify received connector orientation and current before PCB/fabrication.",""
"ENC1","1","PEC11R-4215F-S0024","dawn-dock:PEC11R-4xxxF-Sxxxx","Bourns","PEC11R-4215F-S0024","LCSC","PEC11R-4215F-S0024","1.6301","2026-08-23","24-detent/24-pulse encoder with switch; each contact uses 5V/4.7k wetting; firmware debounce required.",""
"J1","1","USB-C POWER ONLY","Connector_USB:USB_C_Receptacle_GCT_USB4105-xx-A_16P_TopMnt_Horizontal","Global Connector Technology","USB4105-GF-A","DigiKey","11198441","0.65","2026-08-23","Power-only sink; separate CC resistors; D+/D-/SBU intentionally NC; shield to GND.",""
"R1","1","5.1k 1%","Resistor_SMD:R_0603_1608Metric","Yageo","RC0603FR-075K1L","DigiKey","RC0603FR-075K1L","0.005","2026-08-23","USB-C CC1 Rd to GND.",""
"R2","1","5.1k 1%","Resistor_SMD:R_0603_1608Metric","Yageo","RC0603FR-075K1L","DigiKey","RC0603FR-075K1L","0.005","2026-08-23","USB-C CC2 Rd to GND.",""
"R3","1","1.53k 1%","Resistor_SMD:R_0603_1608Metric","Yageo","RC0603FR-071K53L","DigiKey","RC0603FR-071K53L","0.005","2026-08-23","RILM; TI Eq.4 gives 2000/1530+0.04 = 1.347A nominal; conservative +7.5%/-1% estimate 1.463A.",""
"R4","1","10k 1%","Resistor_SMD:R_0603_1608Metric","Yageo","RC0603FR-0710KL","DigiKey","RC0603FR-0710KL","0.005","2026-08-23","Open-drain eFuse FLT pull-up to 3.3V.",""
"R5","1","100k 1%","Resistor_SMD:R_0603_1608Metric","Yageo","RC0603FR-07100KL","DigiKey","RC0603FR-07100KL","0.005","2026-08-23","Backlight control pulldown defaults display dark during reset.",""
"R6","1","100k 1%","Resistor_SMD:R_0603_1608Metric","Yageo","RC0603FR-07100KL","DigiKey","RC0603FR-07100KL","0.005","2026-08-23","microSD chip-select pull-up keeps card inactive during reset.",""
"R7","1","10k 1%","Resistor_SMD:R_0603_1608Metric","Yageo","RC0603FR-0710KL","DigiKey","RC0603FR-0710KL","0.005","2026-08-23","DS3231M INT/SQW open-drain pull-up to 3.3V.",""
"R8,R9","2","4.7k 1% DNP","Resistor_SMD:R_0603_1608Metric","Yageo","RC0603FR-074K7L","DigiKey","RC0603FR-074K7L","0.005","2026-08-23","DNP by default because display/ALS modules include pull-ups; populate only after measured rise-time review.","DNP"
"R10","1","100k 1%","Resistor_SMD:R_0603_1608Metric","Yageo","RC0603FR-07100KL","DigiKey","RC0603FR-07100KL","0.005","2026-08-23","AMP_SD pulldown keeps amplifier shut down through reset.",""
"R11-R15","5","4.7k 1%","Resistor_SMD:R_0603_1608Metric","Yageo","RC0603FR-074K7L","DigiKey","RC0603FR-074K7L","0.005","2026-08-23","Individual 5V contact-wetting pulldown; about 1.06mA when contact closes.",""
"SPK1","1","8ohm 2W Speaker (B)","","Waveshare","8ohm 2W Speaker (B)","Waveshare","27859","1.99","2026-08-23","Off-board enclosed speaker; verify cable termination, SPL, distortion, enclosure heating, and acoustic fit on bench.",""
"SW1","1","SNOOZE","Button_Switch_THT:SW_TH_Tactile_Omron_B3F-10xx","Omron","B3F-1000","LCSC","B3F-1000","0.093","2026-08-23","Large enclosure plunger; 5V/4.7k contact wetting; post-buffer SNOOZE_N remains active low.",""
"SW2","1","BRIGHTNESS","Button_Switch_THT:SW_TH_Tactile_Omron_B3F-10xx","Omron","B3F-1000","LCSC","B3F-1000","0.093","2026-08-23","Separated smaller actuator; 5V/4.7k contact wetting; post-buffer BRIGHTNESS_N active low.",""
"U1","1","DS3231MZ+","Package_SO:SOIC-8_3.9x4.9mm_P1.27mm","Analog Devices / Maxim Integrated","DS3231MZ+","DigiKey","DS3231MZ+","5.50","2026-08-23","Battery-backed RTC; VBAT connects only to primary CR2032; no charge path.",""
"U2","1","TPS259531DSGR","Package_SON:WSON-8-1EP_2x2mm_P0.5mm_EP0.9x1.6mm_ThermalVias","Texas Instruments","TPS259531DSGR","LCSC","C2155674","0.4114","2026-08-23","5.7V-clamp auto-retry eFuse; EN tied high; 1.53k ILM; 100nF dVdt; exposed pad to GND; thermal layout required.",""
"U3","1","SN74LVC14APWR","Package_SO:TSSOP-14_4.4x5mm_P0.65mm","Texas Instruments","SN74LVC14APWR","LCSC","SN74LVC14APWR","0.1498","2026-08-23","3.3V-powered Schmitt inverter; inputs tolerate 5V; five contact channels used; unused 6A tied GND.",""

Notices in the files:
hardware/kicad/dawn-dock.kicad_pcb:
OPEN HARDWARE CERN-OHL-S-2.0
